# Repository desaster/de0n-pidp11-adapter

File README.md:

# DE0-Nano adapter board for PiDP-11

This is an adapter board to connect the
[DE0-Nano  FPGA Development board](http://www.terasic.com.tw/cgi-bin/page/archive.pl?Language=English&No=593)
to the [PiDP-11, PDP-11/70 front panel replica](https://obsolescence.wixsite.com/obsolescence/pidp-11).
It is intended to be used with [PDP2011, an FPGA implementation of PDP-11](http://pdp2011.sytse.net/wordpress/).

In addition to routing the necessary pins to the panel, the board also
includes some components for use with the PDP2011:
* Micro-SDCard connector
* USB-UART bridge using the [CP2102](https://www.silabs.com/products/interface/usb-bridges/classic-usb-bridges/device.cp2102)
* Additional pin headers for a secondary UART connection
* Pin headers for connecting to [PMODNIC100](https://store.digilentinc.com/pmod-nic100-network-interface-controller/)

The pinout is a direct implementation of those
[described by Sytse in his blog](http://pdp2011.sytse.net/wordpress/wiring/).

The components used are basically what I had lying around.
If you wish to make this board yourself, consider changing the design to
match the components most optimal for you.

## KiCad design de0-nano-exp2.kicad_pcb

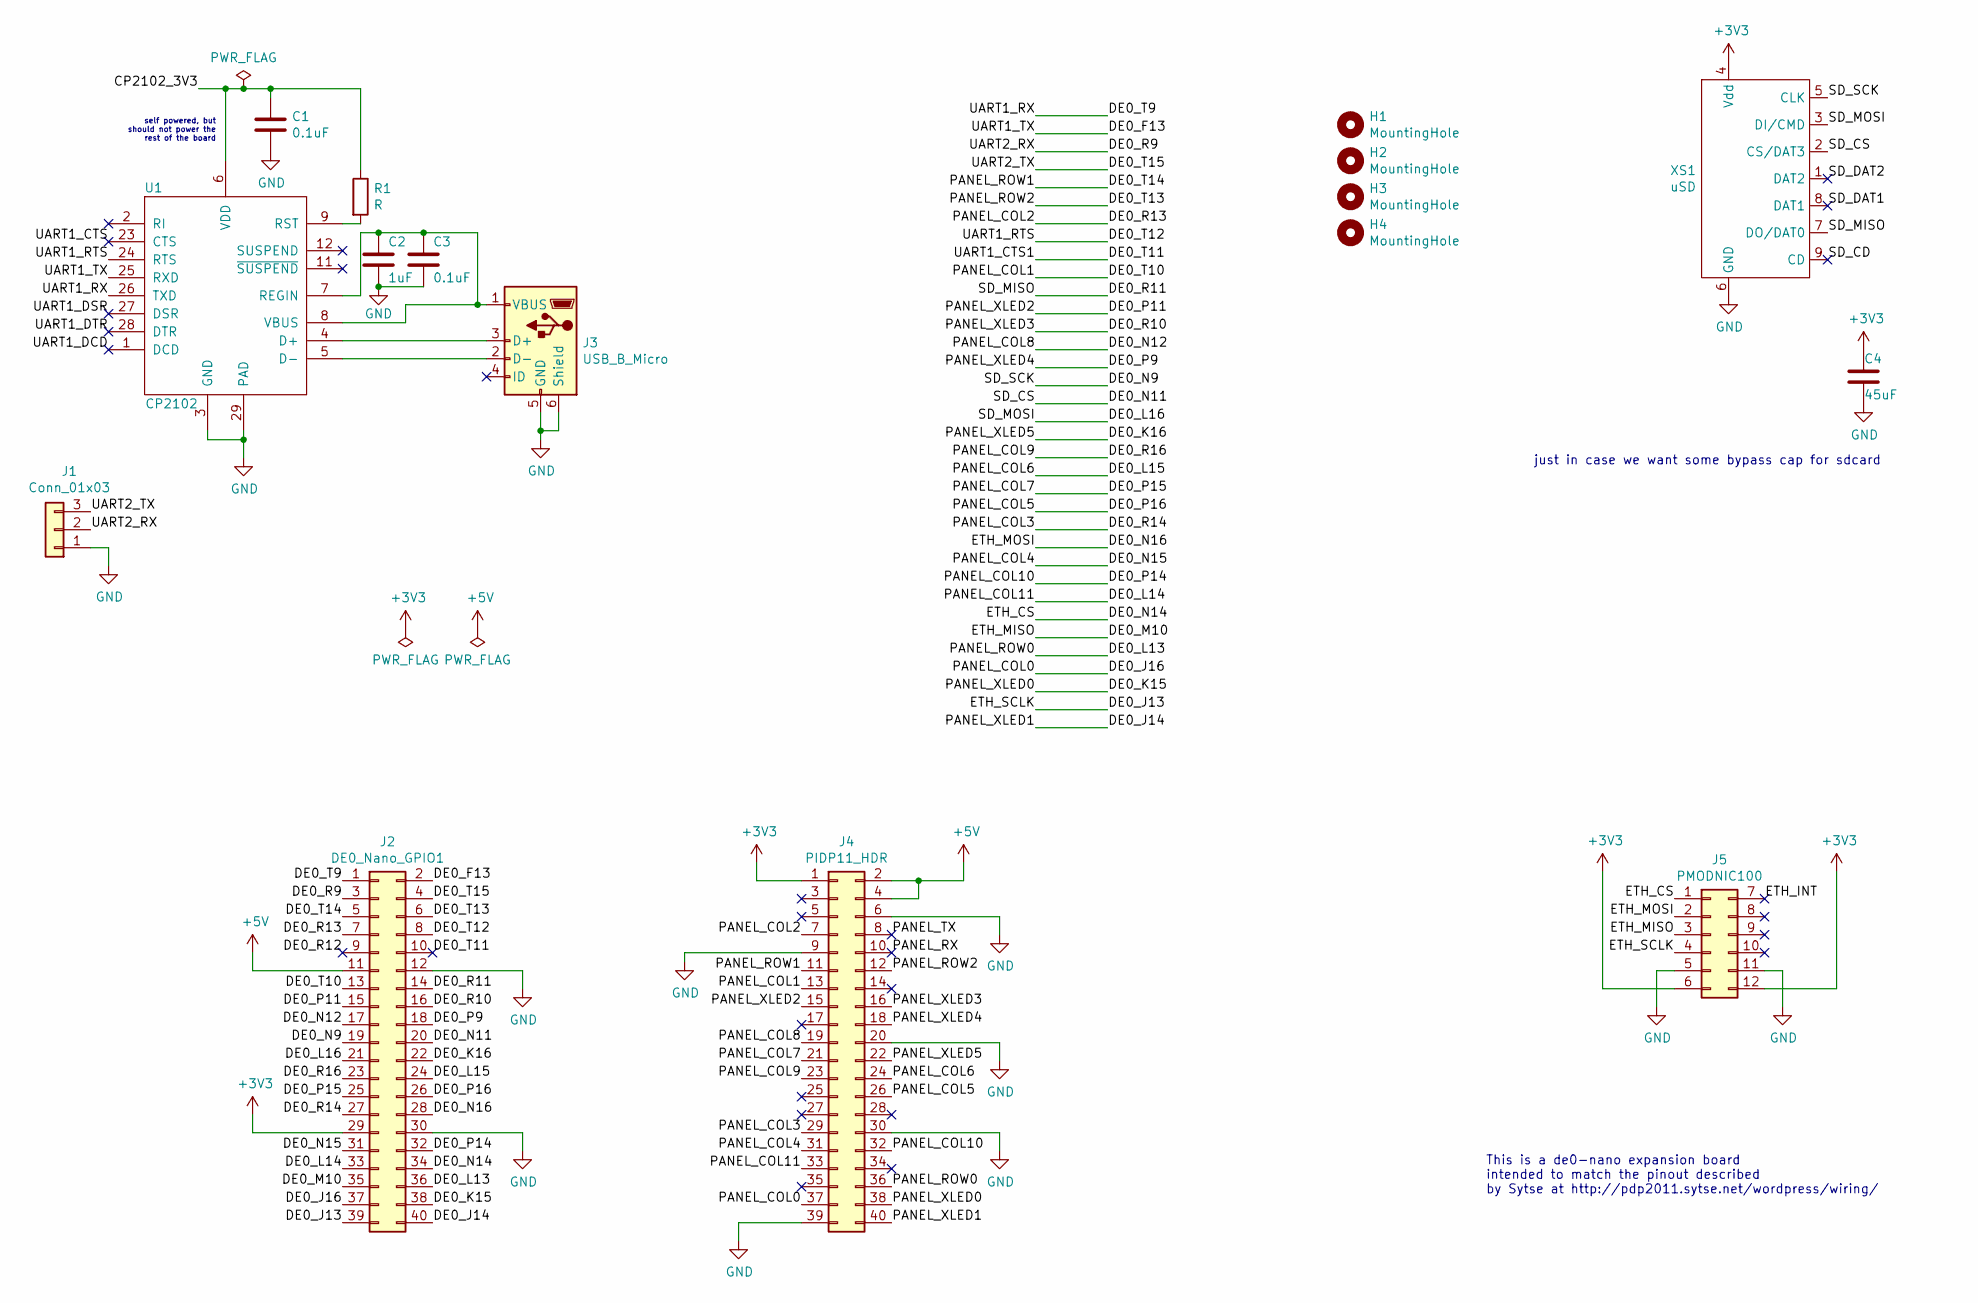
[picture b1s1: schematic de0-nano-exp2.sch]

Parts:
C1, C3: 0.1uF; C_0805_2012Metric_Pad1.15x1.40mm_HandSolder
C2: 1uF; C_0805_2012Metric_Pad1.15x1.40mm_HandSolder
C4: 45uF; C_0805_2012Metric_Pad1.15x1.40mm_HandSolder
H1, H2, H3, H4: MountingHole; MountingHole_RasPI
J1: Conn_01x03; PinHeader_1x03_P2.54mm_Vertical
J2: DE0_Nano_GPIO1; IDC-Header_2x20_P2.54mm_Vertical
J3: USB_B_Micro; USB_Mini-B_Lumberg_2486_01_Horizontal
J4: PIDP11_HDR; PinHeader_2x20_P2.54mm_Vertical
J5: PMODNIC100; pmodnic
R1: R; R_0805_2012Metric_Pad1.15x1.40mm_HandSolder
U1: CP2102; QFN-28-1EP_5x5mm_Pitch0.5mm
XS1: uSD; Conn_uSDcard

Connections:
+3V3: C4.1, J2.29, J4.1, J5.6, J5.12, XS1.4 (Vdd)
+5V: J2.11, J4.2, J4.4
/CP2102_3V3: C1.1, R1.1, U1.6 (VDD)
/DE0_F13: J2.2, U1.25 (RXD)
/DE0_J13: J2.39, J5.4
/DE0_J14: J2.40, J4.40
/DE0_J16: J2.37, J4.37
/DE0_K15: J2.38, J4.38
/DE0_K16: J2.22, J4.22
/DE0_L13: J2.36, J4.36
/DE0_L14: J2.33, J4.33
/DE0_L15: J2.24, J4.24
/DE0_L16: J2.21, XS1.3 (DI/CMD)
/DE0_M10: J2.35, J5.3
/DE0_N9: J2.19, XS1.5 (CLK)
/DE0_N11: J2.20, XS1.2 (CS/DAT3)
/DE0_N12: J2.17, J4.19
/DE0_N14: J2.34, J5.1
/DE0_N15: J2.31, J4.31
/DE0_N16: J2.28, J5.2
/DE0_P9: J2.18, J4.18
/DE0_P11: J2.15, J4.15
/DE0_P14: J2.32, J4.32
/DE0_P15: J2.25, J4.21
/DE0_P16: J2.26, J4.26
/DE0_R9: J1.2, J2.3
/DE0_R10: J2.16, J4.16
/DE0_R11: J2.14, XS1.7 (DO/DAT0)
/DE0_R12: J2.9
/DE0_R13: J2.7, J4.7
/DE0_R14: J2.27, J4.29
/DE0_R16: J2.23, J4.23
/DE0_T9: J2.1, U1.26 (TXD)
/DE0_T10: J2.13, J4.13
/DE0_T11: J2.10
/DE0_T12: J2.8, U1.24 (RTS)
/DE0_T13: J2.6, J4.12
/DE0_T14: J2.5, J4.11
/DE0_T15: J1.3, J2.4
/ETH_INT: J5.7
/PANEL_RX: J4.10
/PANEL_TX: J4.8
/SD_CD: XS1.9 (CD)
/SD_DAT1: XS1.8 (DAT1)
/SD_DAT2: XS1.1 (DAT2)
/UART1_CTS: U1.23 (CTS)
/UART1_DCD: U1.1 (DCD)
/UART1_DSR: U1.27 (DSR)
/UART1_DTR: U1.28 (DTR)
GND: C1.2, C2.2, C3.2, C4.2, J1.1, J2.12, J2.30, J3.5 (GND), J3.6 (Shield), J4.6, J4.9, J4.20, J4.30, J4.39, J5.5, J5.11, U1.3 (GND), U1.29 (PAD), XS1.6 (GND)
unnamed: C2.1, C3.1, J3.1 (VBUS), U1.7 (REGIN), U1.8 (VBUS)
unnamed: J3.2 (D-), U1.5 (D-)
unnamed: J3.3 (D+), U1.4 (D+)
unnamed: R1.2, U1.9 (RST)

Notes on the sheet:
This is a de0-nano expansion board intended to match the pinout described by Sytse at http://pdp2011.sytse.net/wordpress/wiring/
just in case we want some bypass cap for sdcard
self powered, but should not power the rest of the board

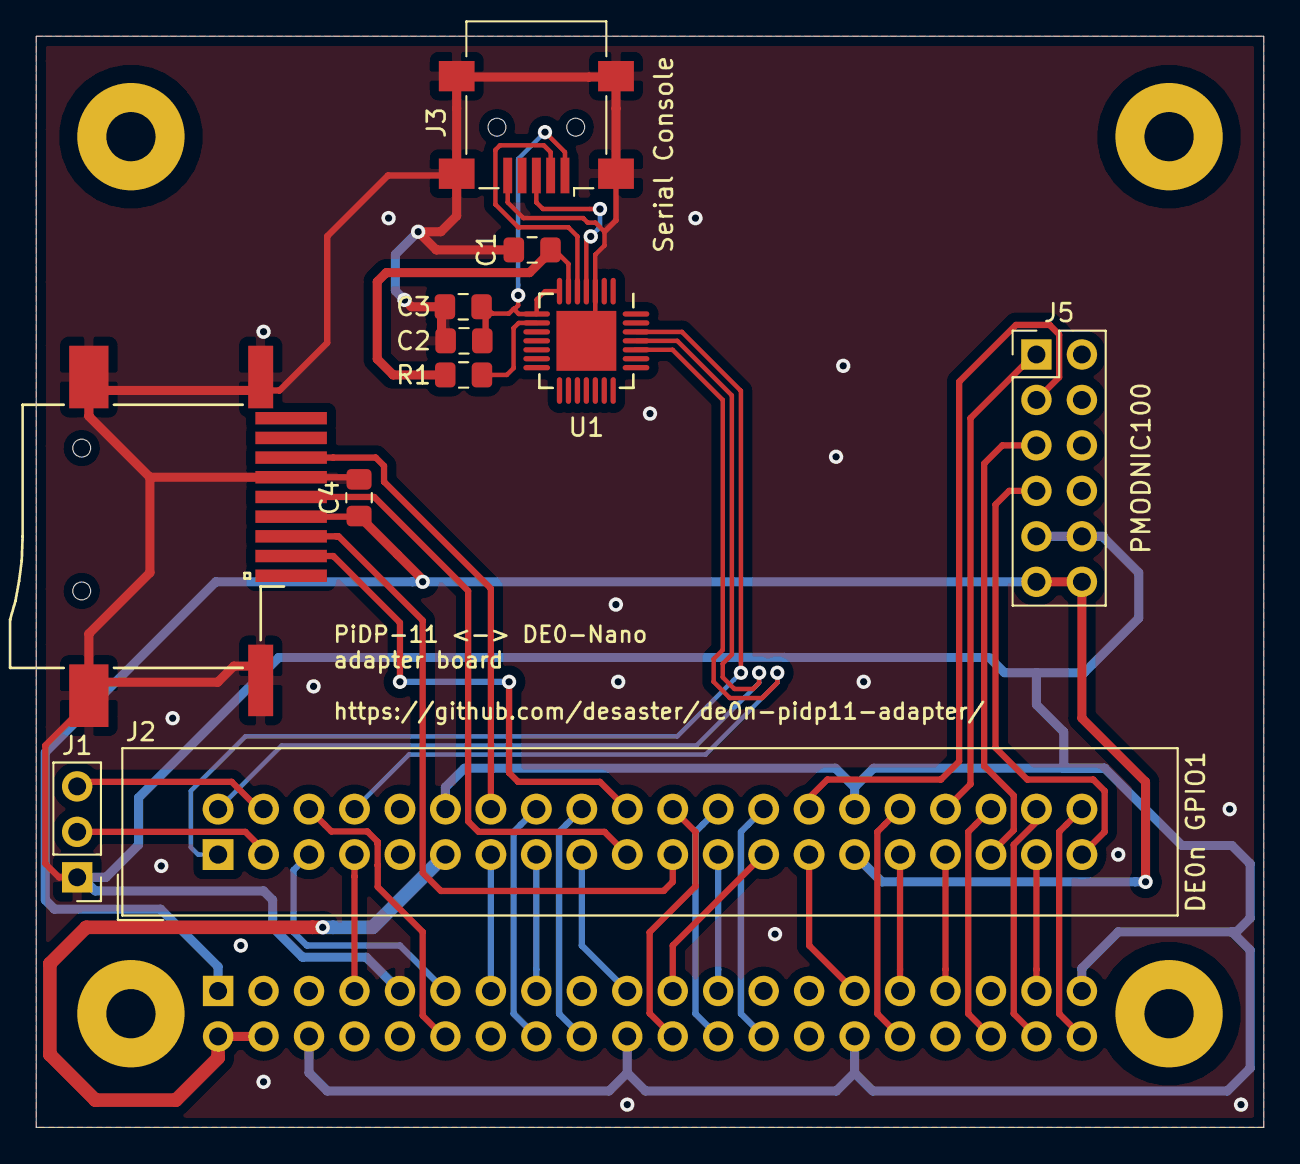
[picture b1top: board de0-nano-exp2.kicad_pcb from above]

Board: 2 copper layers, 68.6 x 61.0 mm, 16 parts (1 on the bottom side), 42 nets.

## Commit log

2019-08-24 fix wrong pin layout for pmod connector
    plus other smaller tweaks
